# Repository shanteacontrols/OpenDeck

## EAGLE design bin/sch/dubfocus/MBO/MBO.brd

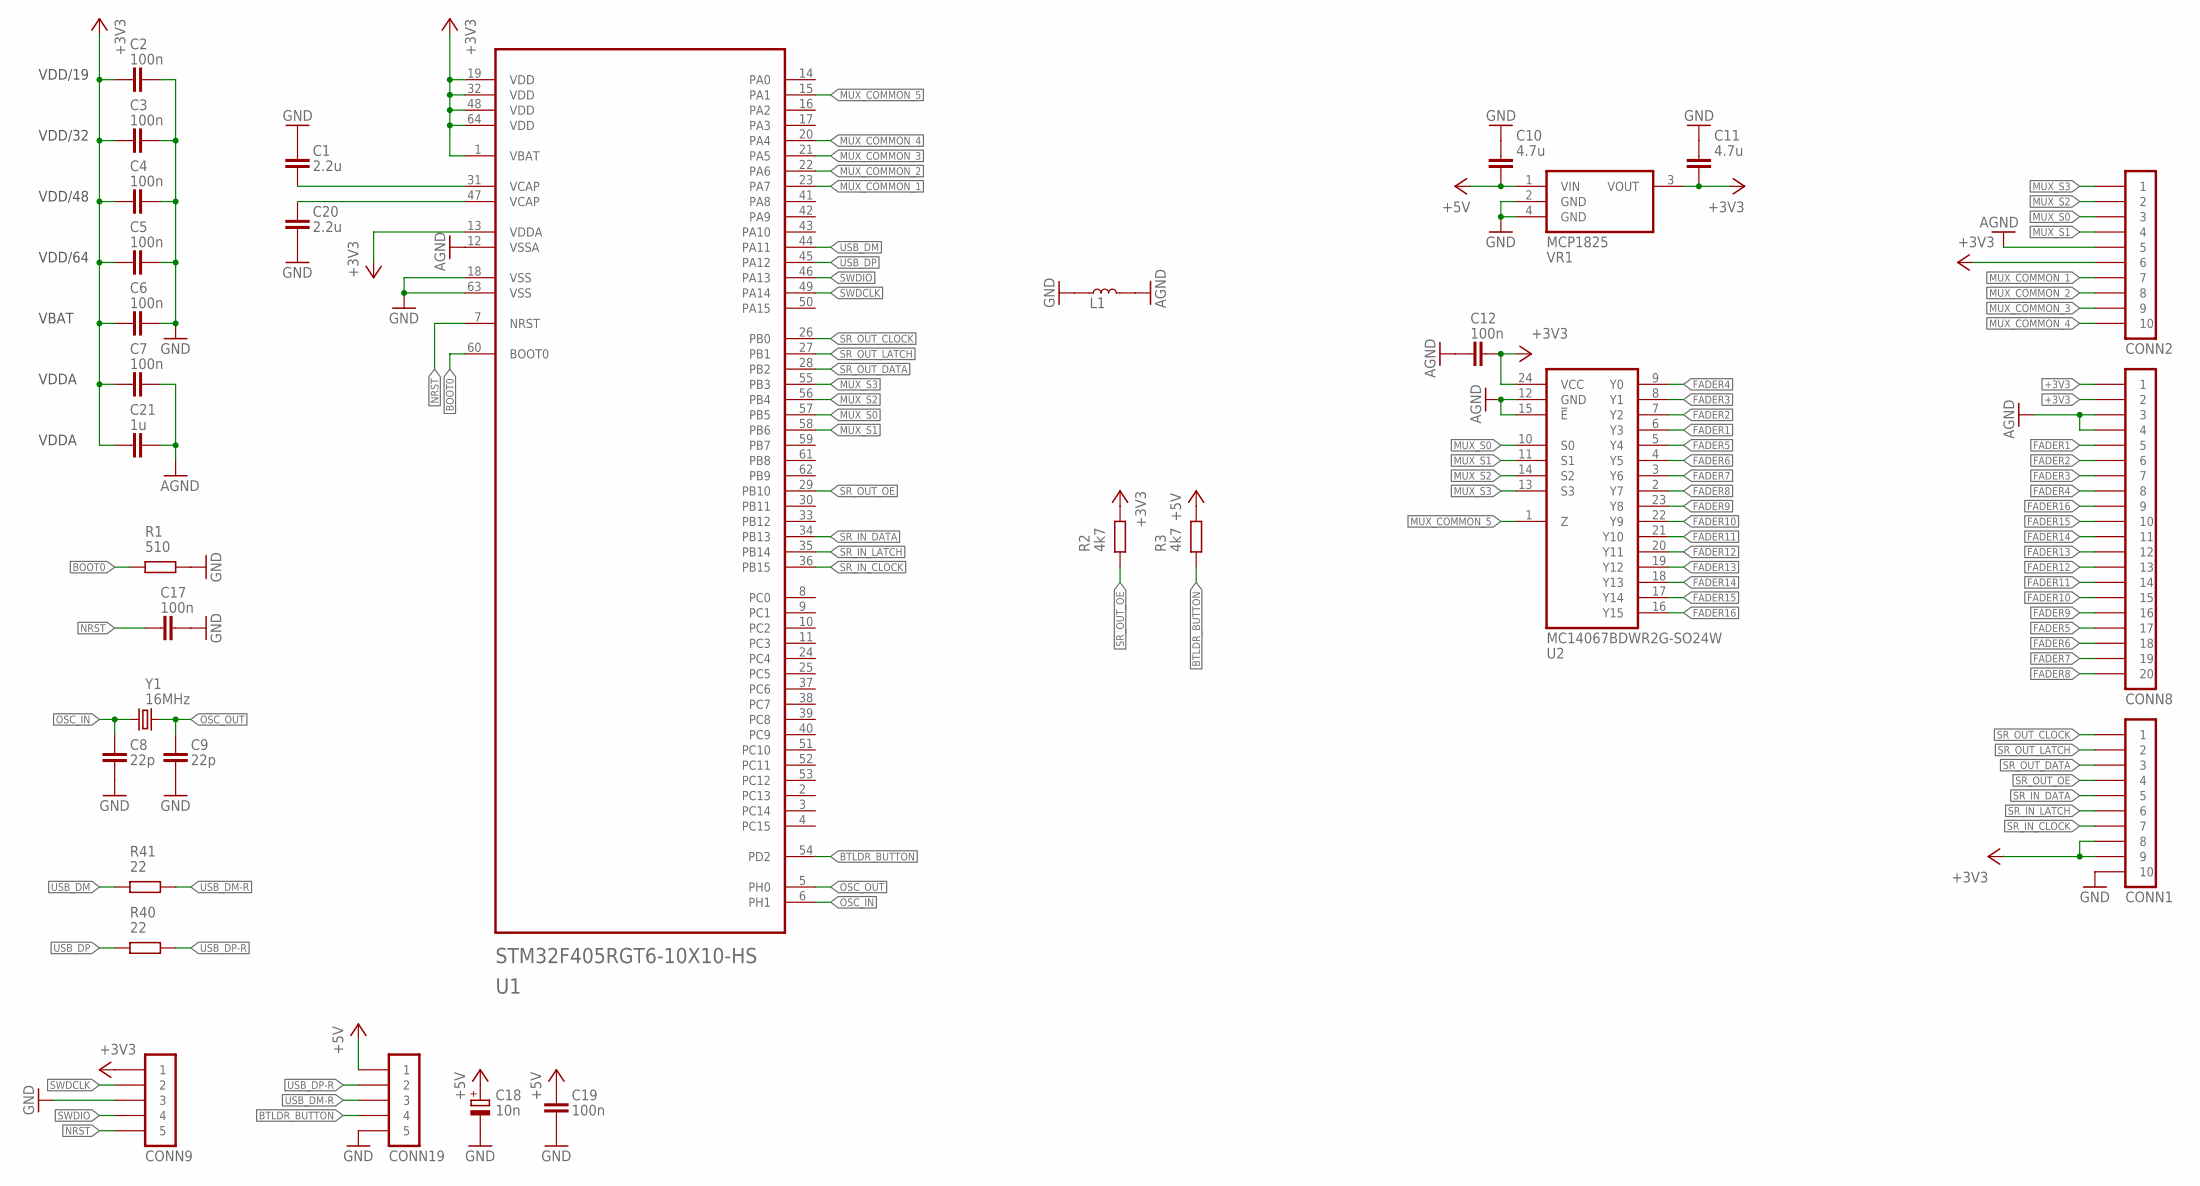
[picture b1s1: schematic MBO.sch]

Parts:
C1, C20: 2.2u; C0805
C2, C3, C4, C5, C6, C7, C12, C17, C19: 100n; C0805
C8, C9: 22p; C0805
C10, C11: 4.7u; C0805
C18: 10n; C-TH-E-0401
C21: 1u; C0805
CONN1, CONN2: PINHD-1X10-FFC-1MM-Z; MOLEX-52271-1079
CONN8: PINHD-1X20-SMD; MOLEX-52271-2079
CONN9: PINHD-1X05-TH-2.54MM; 1X05-2.54
CONN19: PINHD-1X05-JST-XH-H; JST-XH-05P-H
L1: FERRITE_BEAD-BLM21PG221SN1D; L0805
R1: 510; R0805
R2, R3: 4k7; R0805
R40, R41: 22; R0805
U1: STM32F405RGT6-10X10-HS; TQFP-64-10X10-HS
U2: MC14067BDWR2G-SO24W; SO24-W
VR1: MCP1825; SOT223
Y1: 16MHz; HC49US

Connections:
+3V3: C2.1, C3.1, C4.1, C5.1, C6.1, C7.1, C11.1, C12.1, C21.1, CONN1.8, CONN1.9, CONN2.6, CONN8.1, CONN8.2, CONN9.1, R2.2, U1.1 (VBAT), U1.13 (VDDA), U1.19 (VDD), U1.32 (VDD), U1.48 (VDD), U1.64 (VDD), U2.24 (VCC), VR1.3 (VOUT)
+5V: C10.1, C18.+, C19.1, CONN19.1, R3.1, VR1.1 (VIN)
AGND: C7.2, C12.2, C21.2, CONN2.5, CONN8.3, CONN8.4, L1.2, U1.12 (VSSA), U2.12 (GND), U2.15 (!E)
BOOT0: R1.1, U1.60 (BOOT0)
BTLDR_BUTTON: CONN19.4, R3.2, U1.54 (PD2)
FADER1: CONN8.5, U2.6 (Y3)
FADER2: CONN8.6, U2.7 (Y2)
FADER3: CONN8.7, U2.8 (Y1)
FADER4: CONN8.8, U2.9 (Y0)
FADER5: CONN8.17, U2.5 (Y4)
FADER6: CONN8.18, U2.4 (Y5)
FADER7: CONN8.19, U2.3 (Y6)
FADER8: CONN8.20, U2.2 (Y7)
FADER9: CONN8.16, U2.23 (Y8)
FADER10: CONN8.15, U2.22 (Y9)
FADER11: CONN8.14, U2.21 (Y10)
FADER12: CONN8.13, U2.20 (Y11)
FADER13: CONN8.12, U2.19 (Y12)
FADER14: CONN8.11, U2.18 (Y13)
FADER15: CONN8.10, U2.17 (Y14)
FADER16: CONN8.9, U2.16 (Y15)
GND: C1.2, C2.2, C3.2, C4.2, C5.2, C6.2, C8.1, C9.1, C10.2, C11.2, C17.2, C18.-, C19.2, C20.1, CONN1.10, CONN9.3, CONN19.5, L1.1, R1.2, U1.18 (VSS), U1.63 (VSS), VR1.2 (GND), VR1.4 (GND)
MUX_COMMON_1: CONN2.7, U1.23 (PA7)
MUX_COMMON_2: CONN2.8, U1.22 (PA6)
MUX_COMMON_3: CONN2.9, U1.21 (PA5)
MUX_COMMON_4: CONN2.10, U1.20 (PA4)
MUX_COMMON_5: U1.15 (PA1), U2.1 (Z)
MUX_S0: CONN2.3, U1.57 (PB5), U2.10 (S0)
MUX_S1: CONN2.4, U1.58 (PB6), U2.11 (S1)
MUX_S2: CONN2.2, U1.56 (PB4), U2.14 (S2)
MUX_S3: CONN2.1, U1.55 (PB3), U2.13 (S3)
unnamed: C1.1, U1.31 (VCAP)
unnamed: C20.2, U1.47 (VCAP)
NRST: C17.1, CONN9.5, U1.7 (NRST)
OSC_IN: C8.2, U1.6 (PH1), Y1.1
OSC_OUT: C9.2, U1.5 (PH0), Y1.2
SR_IN_CLOCK: CONN1.7, U1.36 (PB15)
SR_IN_DATA: CONN1.5, U1.34 (PB13)
SR_IN_LATCH: CONN1.6, U1.35 (PB14)
SR_OUT_CLOCK: CONN1.1, U1.26 (PB0)
SR_OUT_DATA: CONN1.3, U1.28 (PB2)
SR_OUT_LATCH: CONN1.2, U1.27 (PB1)
SR_OUT_OE: CONN1.4, R2.1, U1.29 (PB10)
SWDCLK: CONN9.2, U1.49 (PA14)
SWDIO: CONN9.4, U1.46 (PA13)
USB_DM: R41.1, U1.44 (PA11)
USB_DM-R: CONN19.3, R41.2
USB_DP: R40.1, U1.45 (PA12)
USB_DP-R: CONN19.2, R40.2

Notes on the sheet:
VDD/19
VDD/32
VDD/48
VDD/64
VBAT
VDDA

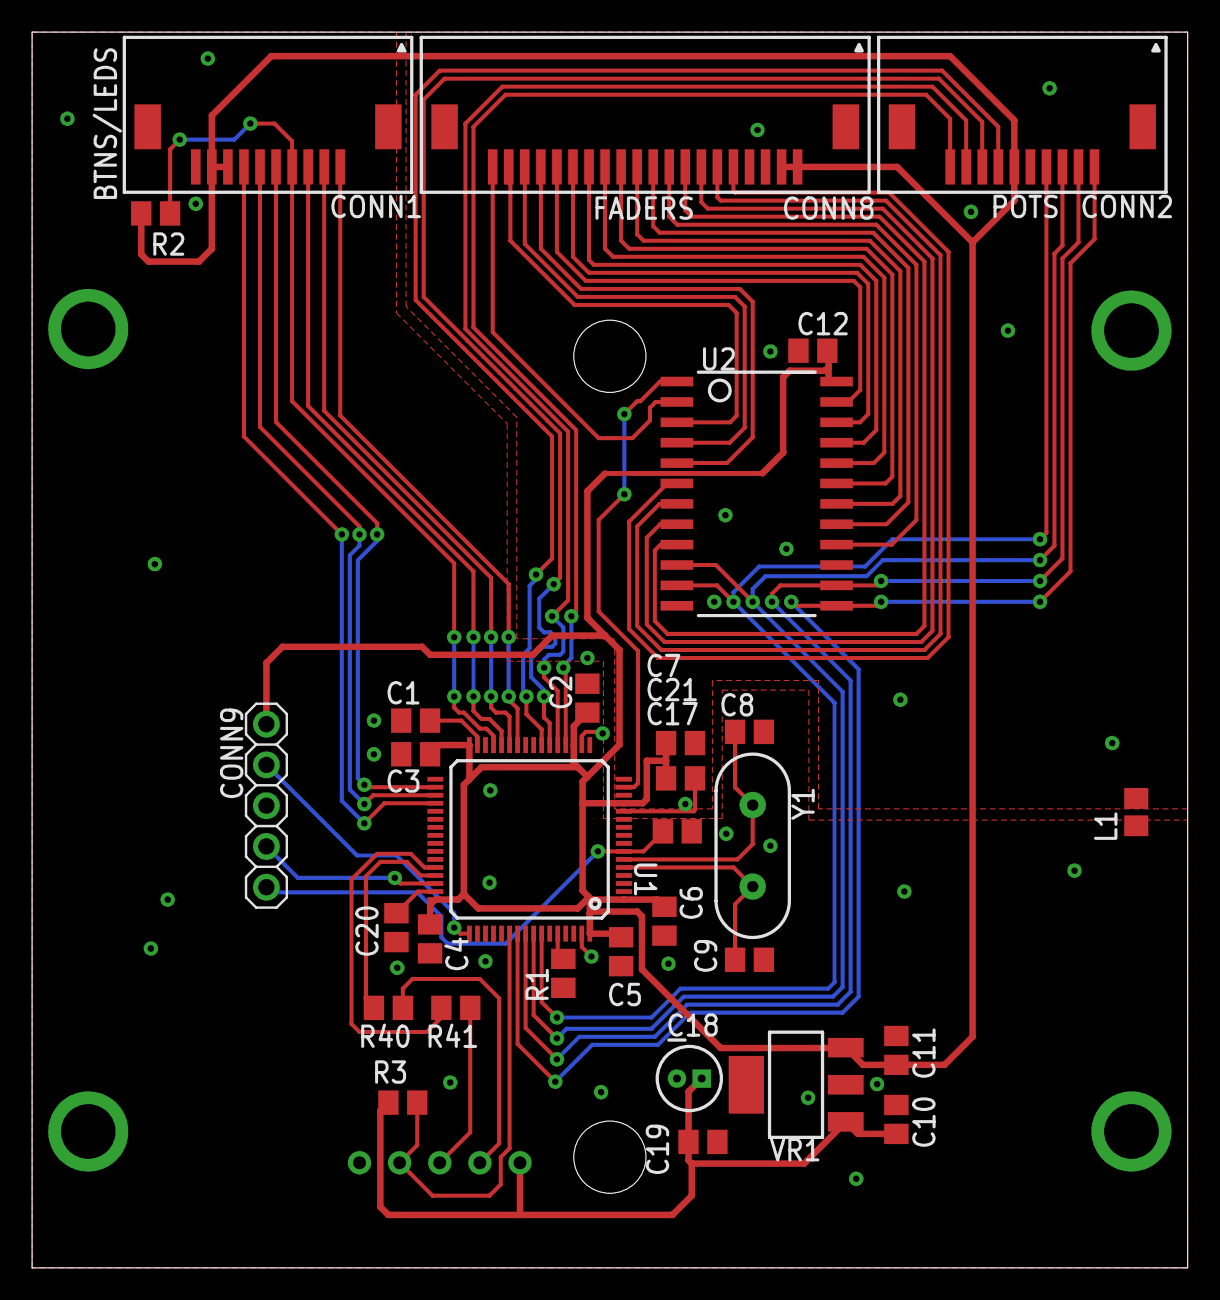
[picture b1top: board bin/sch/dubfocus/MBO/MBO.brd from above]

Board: 2 copper layers, 72.0 x 77.0 mm, 32 parts (1 on the bottom side), 49 nets.

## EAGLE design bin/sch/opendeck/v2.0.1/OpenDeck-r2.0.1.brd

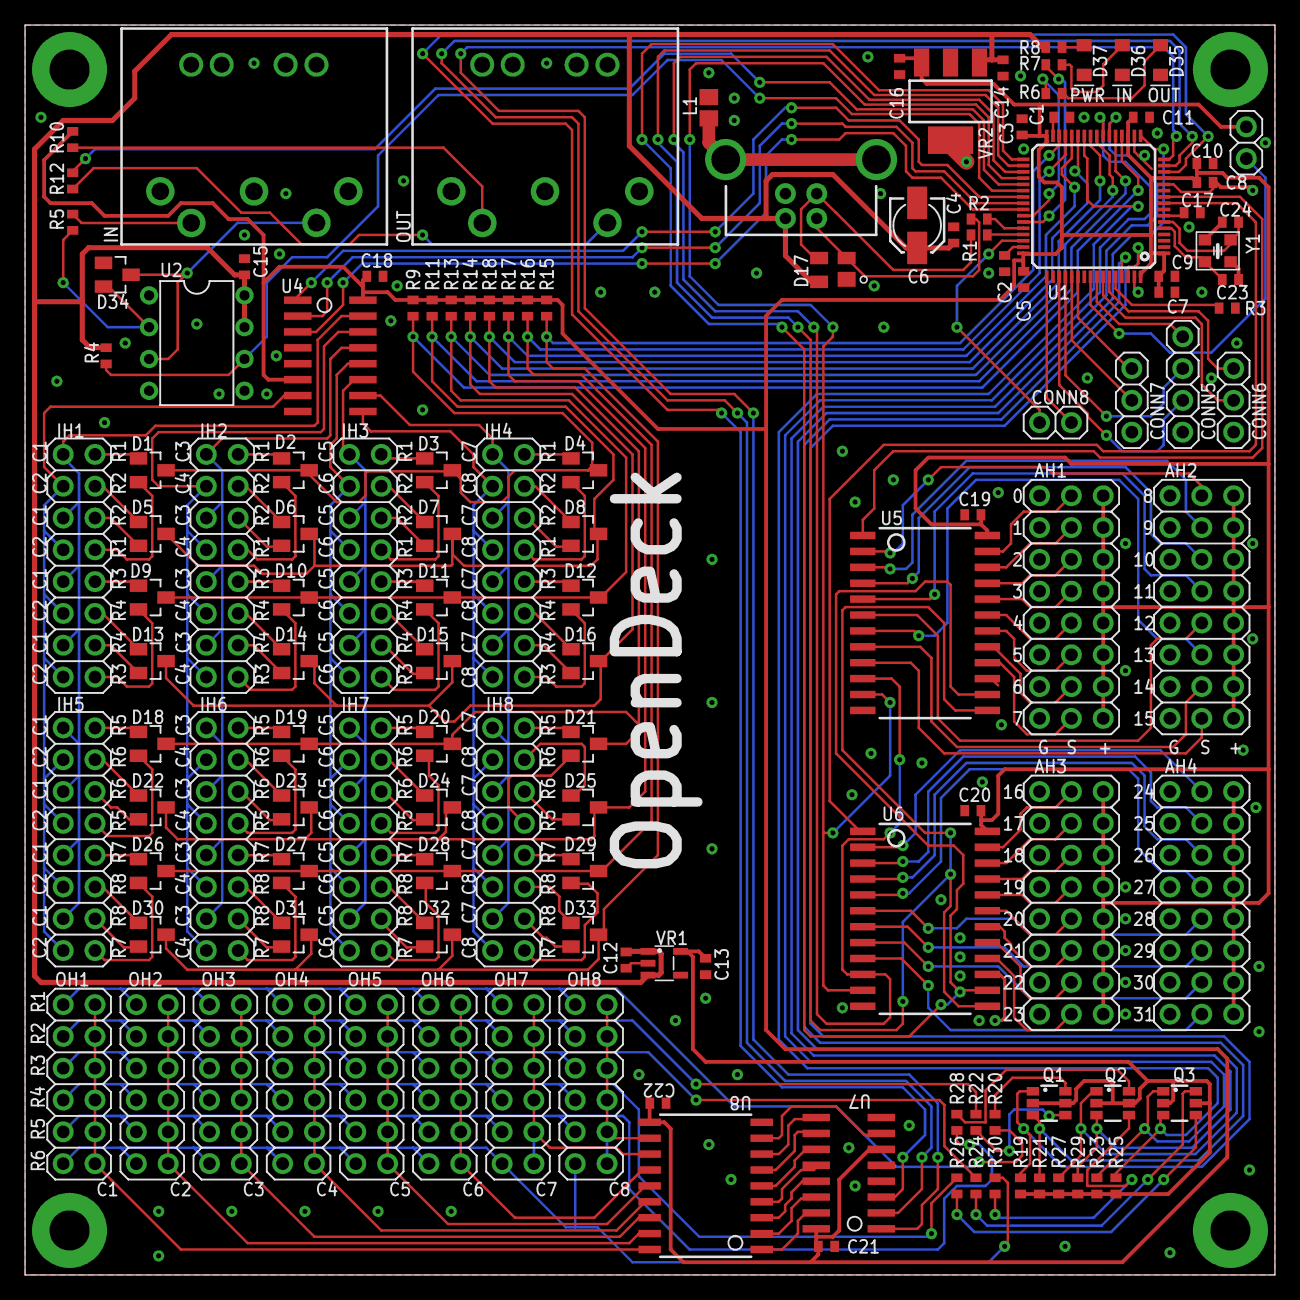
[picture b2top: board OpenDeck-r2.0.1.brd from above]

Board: 2 copper layers, 99.8 x 99.8 mm, 133 parts (0 on the bottom side), 195 nets.

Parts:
AH1, AH2, AH3, AH4: PINHD-3X08; 3X08-2.54
C1, C2: 2.2u; C0402
C3, C4, C5, C7, C8, C9, C10, C11, C15, C17, C18, C19, C20, C21, C22: 100n; C0402
C6: 10u; 153CLV-0405
C12, C13, C14, C16: 4.7u; C0402
C23, C24: 18p; C0402
CONN1: USB-H; USB-B-PTH
CONN2, CONN8: PINHD-1X02-TH-2.54MM; 1X02-2.54-V
CONN3, CONN4: MIDI_CONN-STD; DIN5_SUPPORT
CONN5: PINHD-1X04-TH-2.54MM; 1X04-2.54
CONN6, CONN7: PINHD-1X03-TH-2.54MM; 1X03-2.54-V
D1, D2, D3, D4, D5, D6, D7, D8, D9, D10, D11, D12, D13, D14, D15, D16, D18, D19, D20, D21, D22, D23, D24, D25, D26, D27, D28, D29, D30, D31, D32, D33, D34: BAW56; SOT23
D17: PRTR5V0U2X; SOT143
D35: Red; 0805_LED
D36: Yellow; 0805_LED
D37: Green; 0805_LED
IH1, IH2, IH3, IH4, IH5, IH6, IH7, IH8: PINHD-2X08-TH-2.54MM; 2X08-2.54
L1: FERRITE_BEAD-BLM21PG221SN1D; L0805
OH1, OH2, OH3, OH4, OH5, OH6, OH7, OH8: PINHD-2X06-TH-2.54MM; 2X06-2.54-V
Q1, Q2, Q3: FDC6312P; SSOT6
R1, R2: 22; R0402
R3: 510; R0402
R4: 10k; R0402
R5: 220; R0402
R6, R7, R8: 1k; R0402
R9, R11, R13, R14, R15, R16, R17, R18, R19, R21, R23, R25, R27, R29: 4.7k; R0402
R10: 33; R0402
R12: 10; R0402
R20, R22, R24, R26, R28, R30: 36; R0402
U1: STM32F405RGT6; TQFP-64-10X10
U2: 6N137; DIL08
U4: 74HC138-SO; SO16
U5, U6: MC14067BDWR2G-SO24W; SO24-W
U7: 74HC238-SO; SO16
U8: ULN2803A-SO; SO18
VR1: LP5907-4.5V; SOT23-5
VR2: MCP1825; SOT223
Y1: 16MHz; CRYSTAL-SMD-2.5X2

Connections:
+3V3: AH1.3, AH1.6, AH1.9, AH1.12, AH1.15, AH1.18, AH1.21, AH1.24, AH2.3, AH2.6, AH2.9, AH2.12, AH2.15, AH2.18, AH2.21, AH2.24, AH3.3, AH3.6, AH3.9, AH3.12, AH3.15, AH3.18, AH3.21, AH3.24, AH4.3, AH4.6, AH4.9, AH4.12, AH4.15, AH4.18, AH4.21, AH4.24, C3.1, C5.1, C7.1, C8.1, C9.1, C10.1, C11.1, C16.1, C18.2, C19.2, C20.2, C21.1, C22.1, CONN2.2, R9.1, R10.2, R11.1, R13.1, R14.1, R15.1, R16.1, R17.1, R18.1, U1.1, U1.13, U1.19, U1.32, U1.48, U1.64, U4.6, U4.16, U5.24, U6.24, U7.6, U7.16, U8.10, VR2.3
+5V: C4.2, C6.+, C12.1, C14.1, C15.2, CONN1.VBUS, D17.4, R4.1, R8.1, U2.7, U2.8, VR1.1, VR1.3, VR2.1
A_IN_0: AH1.2, U5.23
A_IN_1: AH1.5, U5.22
A_IN_2: AH1.8, U5.21
A_IN_3: AH1.11, U5.20
A_IN_4: AH1.14, U5.19
A_IN_5: AH1.17, U5.18
A_IN_6: AH1.20, U5.17
A_IN_7: AH1.23, U5.16
A_IN_8: AH2.2, U5.2
A_IN_9: AH2.5, U5.3
A_IN_10: AH2.8, U5.4
A_IN_11: AH2.11, U5.5
A_IN_12: AH2.14, U5.6
A_IN_13: AH2.17, U5.7
A_IN_14: AH2.20, U5.8
A_IN_15: AH2.23, U5.9
A_IN_16: AH3.2, U6.23
A_IN_17: AH3.5, U6.22
A_IN_18: AH3.8, U6.21
A_IN_19: AH3.11, U6.20
A_IN_20: AH3.14, U6.19
A_IN_21: AH3.17, U6.18
A_IN_22: AH3.20, U6.17
A_IN_23: AH3.23, U6.16
A_IN_24: AH4.2, U6.2
A_IN_25: AH4.5, U6.3
A_IN_26: AH4.8, U6.4
A_IN_27: AH4.11, U6.5
A_IN_28: AH4.14, U6.6
A_IN_29: AH4.17, U6.7
A_IN_30: AH4.20, U6.8
A_IN_31: AH4.23, U6.9
BC_1: IH1.1, IH1.5, IH1.9, IH1.13, IH5.1, IH5.5, IH5.9, IH5.13, U4.15
BC_2: IH1.3, IH1.7, IH1.11, IH1.15, IH5.3, IH5.7, IH5.11, IH5.15, U4.7
BC_3: IH2.1, IH2.5, IH2.9, IH2.13, IH6.1, IH6.5, IH6.9, IH6.13, U4.13
BC_4: IH2.3, IH2.7, IH2.11, IH2.15, IH6.3, IH6.7, IH6.11, IH6.15, U4.14
BC_5: IH3.1, IH3.5, IH3.9, IH3.13, IH7.1, IH7.5, IH7.9, IH7.13, U4.11
BC_6: IH3.3, IH3.7, IH3.11, IH3.15, IH7.3, IH7.7, IH7.11, IH7.15, U4.12
BC_7: IH4.1, IH4.5, IH4.9, IH4.13, IH8.1, IH8.5, IH8.9, IH8.13, U4.10
BC_8: IH4.3, IH4.7, IH4.11, IH4.15, IH8.3, IH8.7, IH8.11, IH8.15, U4.9
BOOT0: R3.2, U1.60
BR_1: D1.3, D2.3, D3.3, D4.3, R9.2, U1.20
BR_2: D5.3, D6.3, D7.3, D8.3, R11.2, U1.21
BR_3: D9.3, D10.3, D11.3, D12.3, R13.2, U1.24
BR_4: D13.3, D14.3, D15.3, D16.3, R14.2, U1.25
BR_5: D30.3, D31.3, D32.3, D33.3, R15.2, U1.30
BR_6: D26.3, D27.3, D28.3, D29.3, R16.2, U1.29
BR_7: D22.3, D23.3, D24.3, D25.3, R17.2, U1.28
BR_8: D18.3, D19.3, D20.3, D21.3, R18.2, U1.27
BTLDR_BUTTON: CONN2.1, U1.56
D+: R1.2, U1.45
D+X: CONN1.D+, D17.3, R1.1
D-: R2.1, U1.44
D-X: CONN1.D-, D17.2, R2.2
DEC_DI_A0: U1.39, U4.1
DEC_DI_A1: U1.40, U4.2
DEC_DI_A2: U1.41, U4.3
DEC_DO_A0: U1.16, U7.1
DEC_DO_A1: U1.15, U7.2
DEC_DO_A2: U1.14, U7.3
DEC_LM_Y0: U7.15, U8.1
DEC_LM_Y1: U7.14, U8.2
DEC_LM_Y2: U7.13, U8.3
DEC_LM_Y3: U7.12, U8.4
DEC_LM_Y4: U7.11, U8.5
DEC_LM_Y5: U7.10, U8.6
DEC_LM_Y6: U7.9, U8.7
DEC_LM_Y7: U7.7, U8.8
GND: AH1.1, AH1.4, AH1.7, AH1.10, AH1.13, AH1.16, AH1.19, AH1.22, AH2.1, AH2.4, AH2.7, AH2.10, AH2.13, AH2.16, AH2.19, AH2.22, AH3.1, AH3.4, AH3.7, AH3.10, AH3.13, AH3.16, AH3.19, AH3.22, AH4.1, AH4.4, AH4.7, AH4.10, AH4.13, AH4.16, AH4.19, AH4.22, C1.1, C2.2, C3.2, C4.1, C5.2, C6.-, C7.2, C8.2, C9.2, C10.2, C11.2, C12.2, C13.2, C14.2, C15.1, C16.2, C17.2, C18.1, C19.1, C20.1, C21.2, C22.2, C23.2, C24.2, CONN1.GND, CONN4.2, CONN5.4, CONN6.3, CONN7.3, D17.1, D35.C, D36.C, D37.C, L1.1, R3.1, U1.12, U1.18, U1.63, U2.5, U4.4, U4.5, U4.8, U5.12, U5.15, U6.12, U6.15, U7.4, U7.5, U7.8, U8.9, VR1.2, VR2.2, VR2.4, Y1.2, Y1.4
IH1_2: D1.1, IH1.2
IH1_4: D5.1, IH1.4
IH1_6: D5.2, IH1.6
IH1_8: D1.2, IH1.8
IH1_10: D9.1, IH1.10
IH1_12: D13.1, IH1.12
IH1_14: D13.2, IH1.14
IH1_16: D9.2, IH1.16
IH2_2: D2.1, IH2.2
IH2_4: D6.1, IH2.4
IH2_6: D6.2, IH2.6
IH2_8: D2.2, IH2.8
IH2_10: D10.1, IH2.10
IH2_12: D14.1, IH2.12
IH2_14: D14.2, IH2.14
IH2_16: D10.2, IH2.16
IH3_2: D3.1, IH3.2
IH3_4: D7.1, IH3.4
IH3_6: D7.2, IH3.6
IH3_8: D3.2, IH3.8
IH3_10: D11.1, IH3.10
IH3_12: D15.1, IH3.12
IH3_14: D15.2, IH3.14
IH3_16: D11.2, IH3.16
IH4_2: D4.1, IH4.2
IH4_4: D8.1, IH4.4
IH4_6: D8.2, IH4.6
IH4_8: D4.2, IH4.8
IH4_10: D12.1, IH4.10
IH4_12: D16.1, IH4.12
IH4_14: D16.2, IH4.14
IH4_16: D12.2, IH4.16
IH5_2: D18.1, IH5.2
IH5_4: D22.1, IH5.4
IH5_6: D22.2, IH5.6
IH5_8: D18.2, IH5.8
IH5_10: D26.1, IH5.10
IH5_12: D30.1, IH5.12
IH5_14: D30.2, IH5.14
IH5_16: D26.2, IH5.16
IH6_2: D19.1, IH6.2
IH6_4: D23.1, IH6.4
IH6_6: D23.2, IH6.6
IH6_8: D19.2, IH6.8
IH6_10: D27.1, IH6.10
IH6_12: D31.1, IH6.12
IH6_14: D31.2, IH6.14
IH6_16: D27.2, IH6.16
IH7_2: D20.1, IH7.2
IH7_4: D24.1, IH7.4
IH7_6: D24.2, IH7.6
IH7_8: D20.2, IH7.8
IH7_10: D28.1, IH7.10
IH7_12: D32.1, IH7.12
IH7_14: D32.2, IH7.14
IH7_16: D28.2, IH7.16
IH8_2: D21.1, IH8.2
IH8_4: D25.1, IH8.4
IH8_6: D25.2, IH8.6
IH8_8: D21.2, IH8.8
IH8_10: D29.1, IH8.10
IH8_12: D33.1, IH8.12
IH8_14: D33.2, IH8.14
IH8_16: D29.2, IH8.16
LC_1: OH1.2, OH1.4, OH1.6, OH1.8, OH1.10, OH1.12, U8.18
LC_2: OH2.2, OH2.4, OH2.6, OH2.8, OH2.10, OH2.12, U8.17
LC_3: OH3.2, OH3.4, OH3.6, OH3.8, OH3.10, OH3.12, U8.16
LC_4: OH4.2, OH4.4, OH4.6, OH4.8, OH4.10, OH4.12, U8.15
LC_5: OH5.2, OH5.4, OH5.6, OH5.8, OH5.10, OH5.12, U8.14
LC_6: OH6.2, OH6.4, OH6.6, OH6.8, OH6.10, OH6.12, U8.13
LC_7: OH7.2, OH7.4, OH7.6, OH7.8, OH7.10, OH7.12, U8.12
LC_8: OH8.2, OH8.4, OH8.6, OH8.8, OH8.10, OH8.12, U8.11
LEDS_VCC: C13.1, Q1.2, Q1.5, Q2.2, Q2.5, Q3.2, Q3.5, R19.1, R21.1, R23.1, R25.1, R27.1, R29.1, VR1.5
LR_1_MI: Q1.1, R19.2, U1.62
LR_1_MO: OH1.1, OH2.1, OH3.1, OH4.1, OH5.1, OH6.1, OH7.1, OH8.1, R20.1
LR_1_MO_R: Q1.6, R20.2
LR_2_MI: Q1.3, R21.2, U1.61
LR_2_MO: OH1.3, OH2.3, OH3.3, OH4.3, OH5.3, OH6.3, OH7.3, OH8.3, R22.2
LR_2_MO_R: Q1.4, R22.1
LR_3_MI: Q2.1, R27.2, U1.17
LR_3_MO: OH1.9, OH2.9, OH3.9, OH4.9, OH5.9, OH6.9, OH7.9, OH8.9, R28.1
LR_3_MO_R: Q2.6, R28.2
LR_4_MI: Q2.3, R29.2, U1.22
LR_4_MO: OH1.11, OH2.11, OH3.11, OH4.11, OH5.11, OH6.11, OH7.11, OH8.11, R30.1
LR_4_MO_R: Q3.4, R26.2
LR_5_MI: Q3.1, R23.2, U1.23
LR_5_MO: OH1.5, OH2.5, OH3.5, OH4.5, OH5.5, OH6.5, OH7.5, OH8.5, R24.1
LR_5_MO_R: Q3.6, R24.2
LR_6_MI: Q3.3, R25.2, U1.26
LR_6_MO: OH1.7, OH2.7, OH3.7, OH4.7, OH5.7, OH6.7, OH7.7, OH8.7, R26.1
LR_6_MO_R: Q2.4, R30.2
MIDI_IN: R4.2, U1.38, U2.6
MIDI_IN_4: CONN3.4, R5.1
MIDI_IN_5: CONN3.5, D34.3, U2.3
MIDI_IN_DIODE_OUT: D34.2, R5.2, U2.2
MIDI_IN_LED: R7.2, U1.43
MIDI_IN_LED_R: D36.A, R7.1
MIDI_OUT: R12.2, U1.37
MIDI_OUT_4: CONN4.4, R10.1
MIDI_OUT_5: CONN4.5, R12.1
MIDI_OUT_LED: R6.2, U1.42
MIDI_OUT_LED_R: D35.A, R6.1
MISO: CONN5.2, U1.52
MOSI: CONN5.1, U1.57
MUX_COMMON_1: U1.10, U5.1
MUX_COMMON_2: U1.9, U6.1
MUX_S0: U1.35, U5.10, U6.10
MUX_S1: U1.36, U5.11, U6.11
MUX_S2: U1.33, U5.14, U6.14
MUX_S3: U1.34, U5.13, U6.13
unnamed: C1.2, U1.31
unnamed: C2.1, U1.47
NRST: C17.1, U1.7
OSC_IN: C23.1, U1.5, Y1.1
OSC_OUT: C24.1, U1.6, Y1.3
PWR_LED_R: D37.A, R8.2
SCK: CONN5.3, U1.51
SCL: CONN6.2, U1.58
SDA: CONN6.1, U1.59
SWDCLK: CONN8.2, U1.49
SWDIO: CONN8.1, U1.46
UART_RX: CONN7.1, U1.54
UART_TX: CONN7.2, U1.53
USB_SHIELD: CONN1.S1, CONN1.S2, L1.2

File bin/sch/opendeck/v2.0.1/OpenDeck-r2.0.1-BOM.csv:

Qty,Value,Device,Package,Parts,Description,MANUFACTURER,MPN
1,10,RESISTOR-0402,R0402,R12,Resistor,,
15,100n,CAPACITOR-0402,C0402,"C3, C4, C5, C7, C8, C9, C10, C11, C15, C17, C18, C19, C20, C21, C22",Capacitor,,
1,10k,RESISTOR-0402,R0402,R4,Resistor,,
1,10u,ELECTROLYTIC_CAPACITOR16V-CLV-0405,153CLV-0405,C6,Electrolytic capacitor,Multicomp,MCVVT016M100CA1L
1,16MHz,CRYSTAL-4P-SMD-2.5X2,CRYSTAL-SMD-2.5X2,Y1,Crystal,TXC,8Z-16.000MEEQ-T
2,18p,CAPACITOR-0402,C0402,"C23, C24",Capacitor,,
3,1k,RESISTOR-0402,R0402,"R6, R7, R8",Resistor,,
2,2.2u,CAPACITOR-0402,C0402,"C1, C2",Capacitor,,
2,22,RESISTOR-0402,R0402,"R1, R2",Resistor,,
1,220,RESISTOR-0402,R0402,R5,Resistor,,
1,33,RESISTOR-0402,R0402,R10,Resistor,,
6,36,RESISTOR-0402,R0402,"R20, R22, R24, R26, R28, R30",Resistor,,
14,4.7k,RESISTOR-0402,R0402,"R9, R11, R13, R14, R15, R16, R17, R18, R19, R21, R23, R25, R27, R29",Resistor,,
4,4.7u,CAPACITOR-0402,C0402,"C12, C13, C14, C16",Capacitor,,
1,510,RESISTOR-0402,R0402,R3,Resistor,,
1,6N137,6N137,DIL08,U2,High Speed Optocoupler,Vishay,6N137
1,74HC138-SO,74HC138-SO,SO16,U4,3-to-8 line decoder/demultiplexer; inverting,Nexperia,74HC138D
1,74HC238-SO,74HC238-SO,SO16,U7,74HC238/74HCT238,Nexperia,74HC238D
33,BAW56,BAW56,SOT23,"D1, D2, D3, D4, D5, D6, D7, D8, D9, D10, D11, D12, D13, D14, D15, D16, D18, D19, D20, D21, D22, D23, D24, D25, D26, D27, D28, D29, D30, D31, D32, D33, D34",Small Signal Diode,Multicomp,BAW56-7-F
3,FDC6312P,FDC6312P,SSOT6,"Q1, Q2, Q3",Dual P-channel 1.8V PowerTrench Specified MOSFET,ON Semiconductor,FDC6312P
1,FERRITE_BEAD-BLM21PG221SN1D,FERRITE_BEAD-BLM21PG221SN1D,L0805,L1,Ferrite Bead,Murata,BLM21PG221SN1D
1,Green,LED-0805,0805_LED,D37,LED,,
1,LP5907-4.5V,LP5907-4.5V,SOT23-5,VR1,"Ultra Low-Noise, 250-mA Linear LDO Regulator",Texas Instruments,LP5907MFX-4.5/NOPB
2,MC14067BDWR2G-SO24W,MC14067BDWR2G-SO24W,SO24-W,"U5, U6",16-Channel Analog Multiplexer/Demultiplexer,ON Semiconductor,MC14067BDWR2G
1,MCP1825,MCP1825,SOT223,VR2,"500 mA, Low Voltage, Low Quiescent Current LDO Regulator",Microchip,MCP1825S-3302E/DB
2,MIDI_CONN-STD,MIDI_CONN-STD,DIN5_SUPPORT,"CONN3, CONN4",DIN MIDI connector,,
2,PINHD-1X02-TH-2.54MM,PINHD-1X02-TH-2.54MM,1X02-2.54-V,"CONN2, CONN8",Pin Header,,
2,PINHD-1X03-TH-2.54MM,PINHD-1X03-TH-2.54MM,1X03-2.54-V,"CONN6, CONN7",Pin Header,,
1,PINHD-1X04-TH-2.54MM,PINHD-1X04-TH-2.54MM,1X04-2.54,CONN5,Pin Header,,
8,PINHD-2X06-TH-2.54MM,PINHD-2X06-TH-2.54MM,2X06-2.54-V,"OH1, OH2, OH3, OH4, OH5, OH6, OH7, OH8",Pin Header,,
8,PINHD-2X08-TH-2.54MM,PINHD-2X08-TH-2.54MM,2X08-2.54,"IH1, IH2, IH3, IH4, IH5, IH6, IH7, IH8",Pin Header,,
4,PINHD-3X08,PINHD-3X08,3X08-2.54,"AH1, AH2, AH3, AH4",Pin header,,
1,PRTR5V0U2X,PRTR5V0U2X,SOT143,D17,Ultra low capacitance double rail-to-rail ESD protection diode,Nexperia,PRTR5V0U2X
1,Red,LED-0805,0805_LED,D35,LED,,
1,STM32F405RGT6,STM32F405RGT6,TQFP-64-10X10,U1,ARM Cortex-M4 32b MCU+FPU,ST Microelectronics,STM32F405RGT6
1,ULN2803A-SO,ULN2803A-SO,SO18,U8,ULN2803A Darlington Transistor Arrays,Texas Instruments,ULN2803ADWR
1,USB-H,USB-H,USB-B-PTH,CONN1,"USB B connector, horizontal",,
1,Yellow,LED-0805,0805_LED,D36,LED,,

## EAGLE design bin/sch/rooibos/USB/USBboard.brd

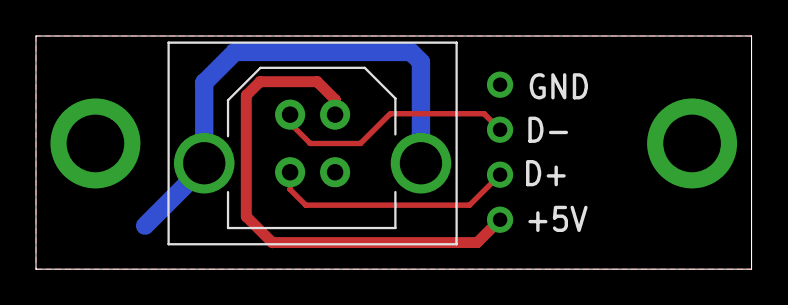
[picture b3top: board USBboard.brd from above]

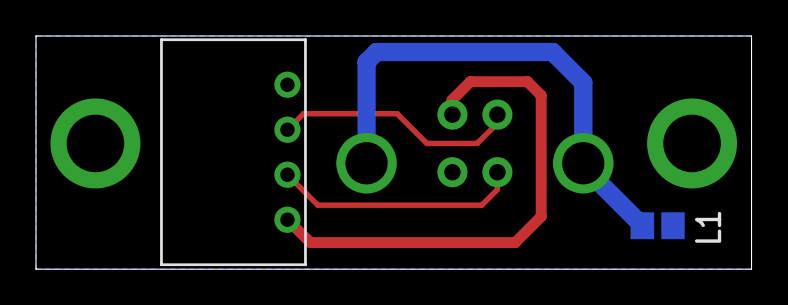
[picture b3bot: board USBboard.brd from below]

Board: 2 copper layers, 39.8 x 13.0 mm, 3 parts (2 on the bottom side), 5 nets.

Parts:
CONN1: USB-B-V; USB-B-PTH-V
CONN2: PINHD-1X04-JST-XH-H; JST-XH-04P-H
L1: FERRITE_BEAD-BLM21PG221SN1D; L0805

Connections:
+5V: CONN1.VBUS, CONN2.1
D+: CONN1.D+, CONN2.2
D-: CONN1.D-, CONN2.3
GND: CONN1.GND, CONN2.4, L1.2
unnamed: CONN1.S1, CONN1.S2, L1.1

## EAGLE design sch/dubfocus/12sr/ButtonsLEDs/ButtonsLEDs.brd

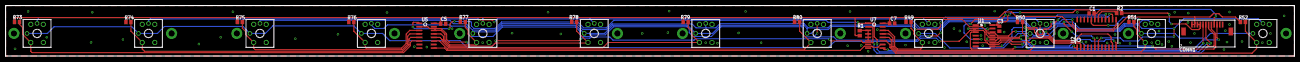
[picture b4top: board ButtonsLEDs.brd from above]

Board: 2 copper layers, 462.6 x 18.1 mm, 35 parts (0 on the bottom side), 34 nets.

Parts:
C1, C3, C5, C7: 100n; C0805
CONN1: PINHD-1X12-SMD; MOLEX-52271-1279
R1, R49, R50, R51, R52, R73, R74, R75, R76, R77, R78, R79, R80: 4k7; R0805
R2: 10k; R0805
SW1, SW2, SW3, SW4, SW5, SW6, SW7, SW8, SW9, SW10, SW11, SW12: OMRON-B3W-9
U1: 74HCT125-SOIC; SOIC14
U2: MAX7219; SO24-W
U5, U7: 74HC165; SO16

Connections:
+3V3: C5.1, C7.1, CONN1.1, CONN1.2, R1.2, R49.2, R50.2, R51.2, R52.2, R73.2, R74.2, R75.2, R76.2, R77.2, R78.2, R79.2, R80.2, U5.16, U7.16
+5V: C1.1, C3.1, CONN1.3, CONN1.4, R2.1, U1.14, U2.19
BUTTON1: R73.1, SW1.1, U5.6
BUTTON2: R74.1, SW2.1, U5.5
BUTTON3: R75.1, SW3.1, U5.4
BUTTON4: R76.1, SW4.1, U5.3
BUTTON5: R77.1, SW5.1, U5.14
BUTTON6: R78.1, SW6.1, U5.13
BUTTON7: R79.1, SW7.1, U5.12
BUTTON8: R80.1, SW8.1, U5.11
BUTTON9: R49.1, SW9.1, U7.14
BUTTON10: R50.1, SW10.1, U7.13
BUTTON11: R51.1, SW11.1, U7.12
BUTTON12: R52.1, SW12.1, U7.11
GND: C1.2, C3.2, C5.2, C7.2, CONN1.11, CONN1.12, SW1.3, SW2.3, SW3.3, SW4.3, SW5.3, SW6.3, SW7.3, SW8.3, SW9.3, SW10.3, SW11.3, SW12.3, U1.1, U1.4, U1.7, U1.10, U2.4, U2.9, U5.8, U5.15, U7.8, U7.15
LED_COLUMN_1: SW1.6-C, SW5.6-C, SW9.6-C, U2.2
LED_COLUMN_2: SW2.6-C, SW6.6-C, SW10.6-C, U2.11
LED_COLUMN_3: SW3.6-C, SW7.6-C, SW11.6-C, U2.6
LED_COLUMN_4: SW4.6-C, SW8.6-C, SW12.6-C, U2.7
LED_ROW_1: SW1.6-A, SW2.6-A, SW3.6-A, SW4.6-A, U2.14
LED_ROW_2: SW5.6-A, SW6.6-A, SW7.6-A, SW8.6-A, U2.16
LED_ROW_3: SW9.6-A, SW10.6-A, SW11.6-A, SW12.6-A, U2.20
unnamed: R1.1, U7.3, U7.4, U7.5, U7.6
unnamed: U1.3, U2.1
unnamed: U1.6, U2.12
unnamed: U1.8, U2.13
unnamed: R2.2, U2.18
SR_IN_CLOCK: CONN1.6, U5.2, U7.2
SR_IN_DAISY_OUT_1: U5.9, U7.10
SR_IN_DATA: CONN1.5, U7.9
SR_IN_LATCH: CONN1.7, U5.1, U7.1
SR_OUT_CLOCK: CONN1.10, U1.9
SR_OUT_DATA: CONN1.8, U1.2
SR_OUT_LATCH: CONN1.9, U1.5

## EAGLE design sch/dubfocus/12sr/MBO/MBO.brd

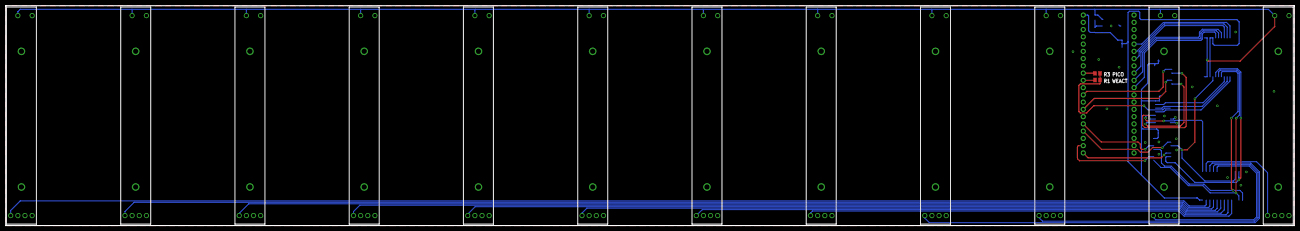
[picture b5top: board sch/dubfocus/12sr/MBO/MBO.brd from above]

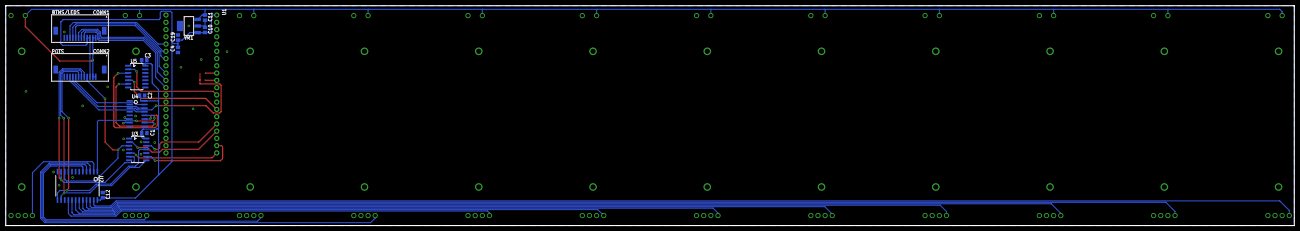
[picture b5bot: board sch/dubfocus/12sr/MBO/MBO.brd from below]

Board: 2 copper layers, 451.1 x 77.0 mm, 30 parts (16 on the bottom side), 40 nets.

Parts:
C1, C2, C3, C12, C19: 100n; C0805
C4: 10u; C0805
C10, C11: 4.7u; C0805
CONN1, CONN2: PINHD-1X12-SMD; MOLEX-52271-1279
FADER1, FADER2, FADER3, FADER4, FADER5, FADER6, FADER7, FADER8, FADER9, FADER10, FADER11, FADER12: RS6011P; RS6011*P
R1, R3: 0; R0805
U1: RASPBERRY_PI_PICO
U2: MC14067BDWR2G-SO24W; SO24-W
U3, U5: 74HCT125-SOIC; SOIC14
U4: 4051; SO16
VR1: MCP1825; SOT223

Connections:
+3V3: C11.1, CONN1.1, CONN1.2, CONN2.1, CONN2.2, FADER1.3, FADER2.3, FADER3.3, FADER4.3, FADER5.3, FADER6.3, FADER7.3, FADER8.3, FADER9.3, FADER10.3, FADER11.3, FADER12.3, VR1.3
+5V: C1.1, C2.1, C3.1, C4.2, C10.1, C12.1, C19.1, CONN1.3, CONN1.4, CONN2.3, U1.40, U2.24, U3.14, U4.16, U5.14, VR1.1
FADER1: FADER1.2, U2.23
FADER2: FADER2.2, U2.22
FADER3: FADER3.2, U2.21
FADER4: FADER4.2, U2.20
FADER5: FADER5.2, U2.19
FADER6: FADER6.2, U2.18
FADER7: FADER7.2, U2.17
FADER8: FADER8.2, U2.16
FADER9: FADER9.2, U2.3
FADER10: FADER10.2, U2.4
FADER11: FADER11.2, U2.5
FADER12: FADER12.2, U2.2
GND: C1.2, C2.2, C3.2, C4.1, C10.2, C11.2, C12.2, C19.2, CONN1.11, CONN1.12, CONN2.11, CONN2.12, FADER1.1, FADER1.S1, FADER1.S2, FADER1.S3, FADER1.S4, FADER1.S5, FADER2.1, FADER2.S1, FADER2.S2, FADER2.S3, FADER2.S4, FADER2.S5, FADER3.1, FADER3.S1, FADER3.S2, FADER3.S3, FADER3.S4, FADER3.S5, FADER4.1, FADER4.S1, FADER4.S2, FADER4.S3, FADER4.S4, FADER4.S5, FADER5.1, FADER5.S1, FADER5.S2, FADER5.S3, FADER5.S4, FADER5.S5, FADER6.1, FADER6.S1, FADER6.S2, FADER6.S3, FADER6.S4, FADER6.S5, FADER7.1, FADER7.S1, FADER7.S2, FADER7.S3, FADER7.S4, FADER7.S5, FADER8.1, FADER8.S1, FADER8.S2, FADER8.S3, FADER8.S4, FADER8.S5, FADER9.1, FADER9.S1, FADER9.S2, FADER9.S3, FADER9.S4, FADER9.S5, FADER10.1, FADER10.S1, FADER10.S2, FADER10.S3, FADER10.S4, FADER10.S5, FADER11.1, FADER11.S1, FADER11.S2, FADER11.S3, FADER11.S4, FADER11.S5, FADER12.1, FADER12.S1, FADER12.S2, FADER12.S3, FADER12.S4, FADER12.S5, U1.3, U1.8, U1.13, U1.18, U1.23, U1.28, U1.33, U1.38, U2.6, U2.7, U2.8, U2.9, U2.12, U2.15, U3.1, U3.4, U3.7, U3.10, U3.13, U4.6, U4.7, U4.8, U4.9, U5.1, U5.4, U5.7, VR1.2, VR1.4
MUX_COMMON: R1.2, R3.2, U4.3
MUX_COMMON_1: CONN2.10, U4.13
MUX_COMMON_2: CONN2.9, U4.14
MUX_COMMON_3: CONN2.8, U4.15
MUX_COMMON_4: U2.1, U4.12
MUX_S0: CONN2.4, U2.10, U3.3
MUX_S0_3V3: U1.24, U3.2
MUX_S1: CONN2.5, U2.11, U3.6
MUX_S1_3V3: U1.21, U3.5
MUX_S2: CONN2.6, U2.14, U3.8
MUX_S2_3V3: U1.22, U3.9
MUX_S3: CONN2.7, U2.13, U3.11
MUX_S3_3V3: U1.25, U3.12
MUX_SEL0_3V3: U1.29, U5.2
MUX_SEL1_3V3: U1.27, U5.5
unnamed: U4.10, U5.6
unnamed: U4.11, U5.3
unnamed: R3.1, U1.32
unnamed: R1.1, U1.31
SR_IN_CLOCK: CONN1.6, U1.10
SR_IN_DATA: CONN1.5, U1.11
SR_IN_LATCH: CONN1.7, U1.9
SR_OUT_CLOCK: CONN1.10, U1.5
SR_OUT_DATA: CONN1.8, U1.7
SR_OUT_LATCH: CONN1.9, U1.6

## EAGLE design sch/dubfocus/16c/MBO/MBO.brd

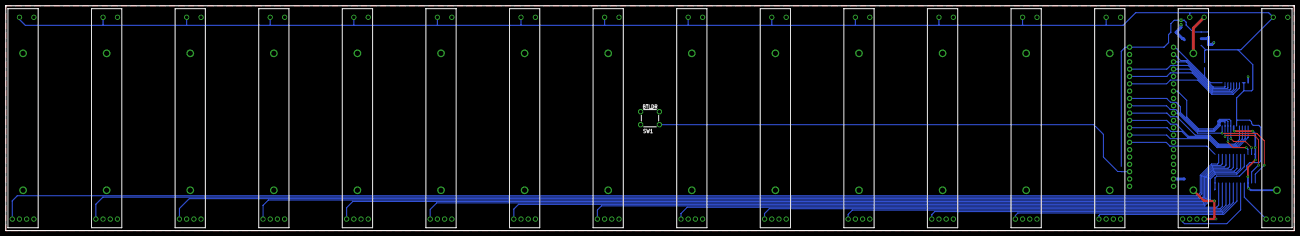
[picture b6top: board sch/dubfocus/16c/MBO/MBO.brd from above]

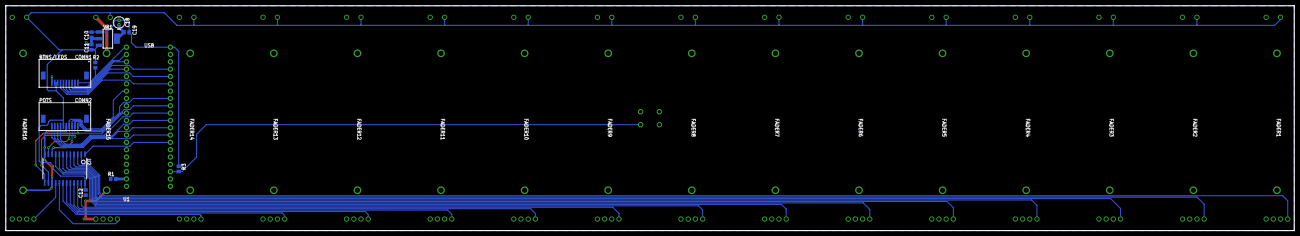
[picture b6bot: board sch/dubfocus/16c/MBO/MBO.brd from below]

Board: 2 copper layers, 447.0 x 78.0 mm, 30 parts (13 on the bottom side), 37 nets.

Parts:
C10, C11: 4.7u; C0805
C12, C19: 100n; C0805
C18: 10n; C-TH-E-0401
CONN1, CONN2: PINHD-1X10-FFC-1MM-Z; MOLEX-52271-1079
FADER1, FADER2, FADER3, FADER4, FADER5, FADER6, FADER7, FADER8, FADER9, FADER10, FADER11, FADER12, FADER13, FADER14, FADER15, FADER16: RS6011P; RS6011*P
R1: 0; R0805
R2, R3: 4k7; R0805
SW1: TACT_SW_6X6MM
U1: STM32F411-BLACK_PILL
U2: MC14067BDWR2G-SO24W; SO24-W
VR1: MCP1825; SOT223

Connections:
+3V3: C11.1, C12.1, CONN1.8, CONN1.9, CONN2.6, FADER1.3, FADER2.3, FADER3.3, FADER4.3, FADER5.3, FADER6.3, FADER7.3, FADER8.3, FADER9.3, FADER10.3, FADER11.3, FADER12.3, FADER13.3, FADER14.3, FADER15.3, FADER16.3, R2.2, U2.24, VR1.3
+5V: C10.1, C18.+, C19.1, R3.1, U1.P2.1, VR1.1
AGND: C12.2, CONN2.5, FADER1.1, FADER1.S1, FADER1.S2, FADER1.S3, FADER1.S4, FADER1.S5, FADER2.1, FADER2.S1, FADER2.S2, FADER2.S3, FADER2.S4, FADER2.S5, FADER3.1, FADER3.S1, FADER3.S2, FADER3.S3, FADER3.S4, FADER3.S5, FADER4.1, FADER4.S1, FADER4.S2, FADER4.S3, FADER4.S4, FADER4.S5, FADER5.1, FADER5.S1, FADER5.S2, FADER5.S3, FADER5.S4, FADER5.S5, FADER6.1, FADER6.S1, FADER6.S2, FADER6.S3, FADER6.S4, FADER6.S5, FADER7.1, FADER7.S1, FADER7.S2, FADER7.S3, FADER7.S4, FADER7.S5, FADER8.1, FADER8.S1, FADER8.S2, FADER8.S3, FADER8.S4, FADER8.S5, FADER9.1, FADER9.S1, FADER9.S2, FADER9.S3, FADER9.S4, FADER9.S5, FADER10.1, FADER10.S1, FADER10.S2, FADER10.S3, FADER10.S4, FADER10.S5, FADER11.1, FADER11.S1, FADER11.S2, FADER11.S3, FADER11.S4, FADER11.S5, FADER12.1, FADER12.S1, FADER12.S2, FADER12.S3, FADER12.S4, FADER12.S5, FADER13.1, FADER13.S1, FADER13.S2, FADER13.S3, FADER13.S4, FADER13.S5, FADER14.1, FADER14.S1, FADER14.S2, FADER14.S3, FADER14.S4, FADER14.S5, FADER15.1, FADER15.S1, FADER15.S2, FADER15.S3, FADER15.S4, FADER15.S5, FADER16.1, FADER16.S1, FADER16.S2, FADER16.S3, FADER16.S4, FADER16.S5, R1.2, U2.12, U2.15
BTLDR_BUTTON: R3.2, SW1.A1, U1.P2.18
FADER1: FADER1.2, U2.2
FADER2: FADER2.2, U2.3
FADER3: FADER3.2, U2.4
FADER4: FADER4.2, U2.5
FADER5: FADER5.2, U2.6
FADER6: FADER6.2, U2.7
FADER7: FADER7.2, U2.8
FADER8: FADER8.2, U2.9
FADER9: FADER9.2, U2.23
FADER10: FADER10.2, U2.22
FADER11: FADER11.2, U2.21
FADER12: FADER12.2, U2.20
FADER13: FADER13.2, U2.19
FADER14: FADER14.2, U2.18
FADER15: FADER15.2, U2.17
FADER16: FADER16.2, U2.16
GND: C10.2, C11.2, C18.-, C19.2, CONN1.10, R1.1, SW1.B1, U1.P1.19, U1.P2.2, VR1.2, VR1.4
MUX_COMMON_1: CONN2.10, U1.P2.13
MUX_COMMON_2: CONN2.9, U1.P2.12
MUX_COMMON_3: CONN2.8, U1.P2.11
MUX_COMMON_4: CONN2.7, U1.P2.10
MUX_COMMON_5: U1.P2.14, U2.1
MUX_S0: CONN2.3, U1.P2.8, U2.10
MUX_S1: CONN2.4, U1.P1.7, U2.11
MUX_S2: CONN2.2, U1.P2.9, U2.14
MUX_S3: CONN2.1, U1.P1.10, U2.13
SR_IN_CLOCK: CONN1.6, U1.P2.5
SR_IN_DATA: CONN1.5, U1.P1.4
SR_IN_LATCH: CONN1.7, U1.P2.6
SR_OUT_CLOCK: CONN1.4, U1.P2.4
SR_OUT_DATA: CONN1.2, U1.P1.2
SR_OUT_LATCH: CONN1.3, U1.P1.3
SR_OUT_OE: CONN1.1, R2.1, U1.P1.1
